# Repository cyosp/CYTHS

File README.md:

# CYTHS

A 433 MHz Temperature and Humidity Solution

This project is divided in several parts:
 * [A sensor](hardware/sensor/V2.0) which measures and sends temperature and humidity

 * [A hardware](hardware/piTransceiver/V1.0) part connected to a [Raspberry Pi](https://www.raspberrypi.org/products/) in order to:
    * Receive sensors information
    * Drive RSL switch connected to electric heaters

 * A software part hosted by the [Raspberry Pi](https://www.raspberrypi.org/products/) which:
    * Drives RSL switches

    * Stores sensors data received

    * Allow to schedule RSL switches change

    * Allow to associate and dissociate switches 

## Hardware requirement

[CYTHS](https://github.com/cyosp/CYTHS) works on [Raspberry Pi](https://www.raspberrypi.org/products/)

It has been tested on models:

 * [Pi 2 Model B](https://www.raspberrypi.org/products/raspberry-pi-2-model-b/)

   Which was used during development phase
 
 * [Pi 3 Model B](https://www.raspberrypi.org/products/raspberry-pi-3-model-b/)
 
   On this board Bluetooth has been added and connected to default UART
 
   To have it working you need:
   
   * Disable Bluetooth to restore default UART

        ```bash
        echo -e "\n# Disable Bluetooth to restore default UART\ndtoverlay=pi3-disable-bt\n" | sudo tee --append /boot/config.txt > /dev/null
        ```
   * Stop Bluetooth service

        ```bash
        sudo systemctl disable hciuart
        ```

    * Make sure you have `console=ttyAMA0` in `/boot/cmdline.txt`

   * And reboot system: `sudo reboot`

## License

**[CYTHS](https://github.com/cyosp/CYTHS)** is released under the BSD 3-Clause License.

See the bundled `LICENSE.md` for details.

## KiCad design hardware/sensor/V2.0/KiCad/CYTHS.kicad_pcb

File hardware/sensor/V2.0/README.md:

## 433 MHz Temperature and Humidity Sensor

### Printed Circuit Board (PCB)

PCB is double layers and has been:
 * Designed using: [KiCad](http://kicad-pcb.org)
 * Printed with: [OSHPARK](https://oshpark.com)

&nbsp;&nbsp;&nbsp;&nbsp;&nbsp;&nbsp;&nbsp;&nbsp;&nbsp;&nbsp;&nbsp;

### Components

| Description                     | Reference                                                                                                         | Power (V) |
|:--------------------------------|:------------------------------------------------------------------------------------------------------------------|-----------|
| Temperature and humidity sensor | [DHT22](https://www.waveshare.com/wiki/DHT22_Temperature-Humidity_Sensor)                                         | 3.3 → 6   |
| Microcontroller                 | [ATTINY85-20SU](https://www.microchip.com/en-us/product/attiny85)                                                 | 2.7 → 5.5 |
| 433 MHz transmitter             | [433 MHz transmitter](https://microcontrollerslab.com/433mhz-rf-transmitter-module-pinout-examples-applications/) | 3.3 → 12  |
| 3x 1.5V AAA batteries           | [Camelion batteries](http://camelionbatteries.com/primary/plus.html)                                              | 1.5       |

#### ATtiny85 pin mapping

```
PB5 -| °   |- VCC
PB3 -|     |- PB2
PB4 -|     |- PB1
GND -|     |- PB0
```

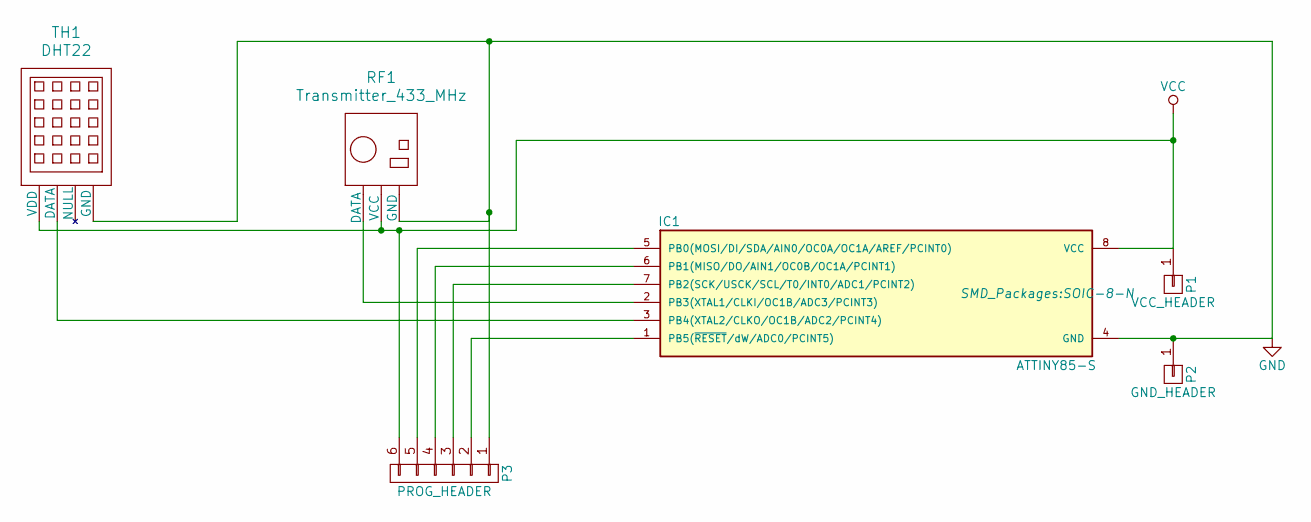
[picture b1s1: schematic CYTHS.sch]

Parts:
IC1: ATTINY85-S; SOIC-8-N
P1: VCC_HEADER; Pin_Header_Straight_1x01
P2: GND_HEADER; Pin_Header_Straight_1x01
P3: PROG_HEADER; Pin_Header_Angled_1x06
RF1: Transmitter_433_MHz; RF_Transmitter_433_MHz
TH1: DHT22; DHT22_Temperature_Humidity

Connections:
GND: IC1.4 (GND), P2.1, P3.1, RF1.3 (GND), TH1.4 (GND)
unnamed: IC1.1 (PB5(~RESET~/dW/ADC0/PCINT5)), P3.2
unnamed: IC1.2 (PB3(XTAL1/CLKI/OC1B/ADC3/PCINT3)), RF1.1 (DATA)
unnamed: IC1.3 (PB4(XTAL2/CLKO/OC1B/ADC2/PCINT4)), TH1.2 (DATA)
unnamed: IC1.5 (PB0(MOSI/DI/SDA/AIN0/OC0A/OC1A/AREF/PCI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), P3.5
unnamed: IC1.6 (PB1(MISO/DO/AIN1/OC0B/OC1A/PCINT1)), P3.4
unnamed: IC1.7 (PB2(SCK/USCK/SCL/T0/INT0/ADC1/PCINT2)), P3.3
VCC: IC1.8 (VCC), P1.1, P3.6, RF1.2 (VCC), TH1.1 (VDD)

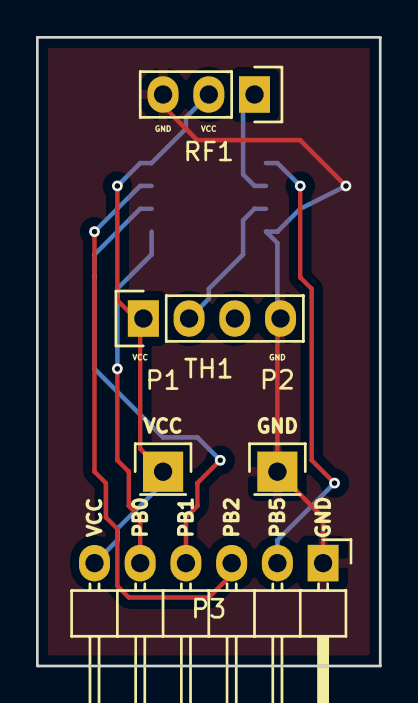
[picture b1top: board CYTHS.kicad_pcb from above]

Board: 2 copper layers, 19.0 x 34.9 mm, 6 parts (1 on the bottom side), 8 nets.

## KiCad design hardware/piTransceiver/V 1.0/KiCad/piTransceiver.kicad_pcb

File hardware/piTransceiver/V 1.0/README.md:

## piTransceiver

[Raspberry Pi](https://www.raspberrypi.org/products/) extension board to receive and transmit to 433MHz.

#### PCB

piTransceiver is composed of a double layer PCB:

&nbsp;&nbsp;&nbsp;&nbsp;&nbsp;&nbsp;&nbsp;&nbsp;&nbsp;&nbsp;&nbsp;

### Components

Components used are:

| Component | Reference                            |
|:----------|:-------------------------------------|
| R1        | 2.2 KΩ 5%                            |
| R2        | 27 Ω 5%                              |
| LED       | Yellow LED                           |
| IC1       | ATtiny85-20PU                        |
| RF1       | 433 MHz transmitter + spring antenna |
| RF2       | 433 MHz receiver + spring antenna    |

#### Configuration

These steps will configure Arduino software in order to use the microcontroller running at 16 Mhz:
 * File -> Preferences
  * In *Additional Boards Manager URLs:*
  * Enter *https://raw.githubusercontent.com/damellis/attiny/ide-1.6.x-boards-manager/package_damellis_attiny_index.json*
  * And *OK* button
 * Tools -> Board-> Boards Manager...
    * Search in the list and select: **attiny** by **David A. Mellis**
    * Click *Install*
    * And *Close* button
 * Tools -> Board-> ATtiny25/45/85
 * Tools -> Processor-> ATtiny85
 * Tools -> Clock-> Internal 16 MHz
 * Tools -> Programmer-> USBtinyISP

Then it's necessary to burn fuses of the microcontroller to set this configuration.
Steps are:
 * Plug a microcontroller on the [Tiny AVR Programmer](https://www.sparkfun.com/products/11801)
 * Plug the [Tiny AVR Programmer](https://www.sparkfun.com/products/11801) to the computer
 * Tools -> Burn Bootloader

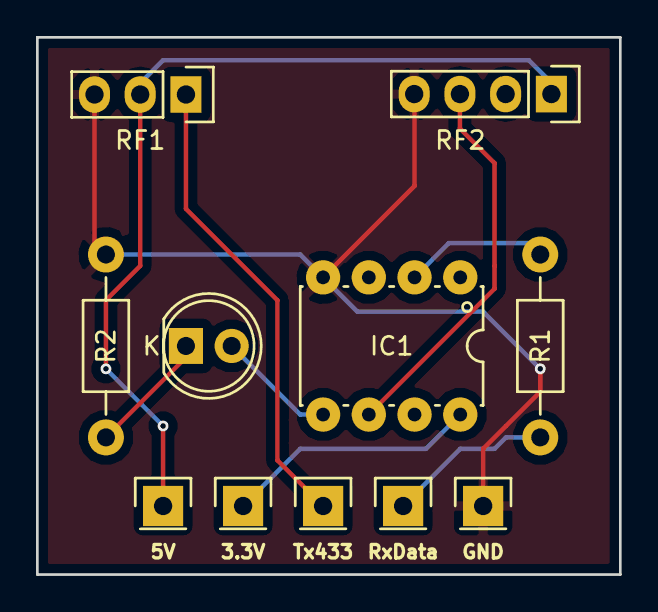
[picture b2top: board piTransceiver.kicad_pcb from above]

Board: 2 copper layers, 32.4 x 29.8 mm, 5 parts (0 on the bottom side), 4 nets.

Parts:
IC1: ATTINY85-S; PDIP-8
R1, R2: Resistor_Horizontal_RM10mm
RF1: RF_Transmitter_433_MHz
RF2: RF_Receiver_433_MHz

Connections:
+5V: RF1.2, RF2.1
GND: IC1.4, R2.1, RF1.3, RF2.4
unnamed: IC1.2, R1.1
unnamed: IC1.6, RF2.3

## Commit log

2016-03-16 Update README file
2016-03-17 Improve project description
2016-03-26 Improve README file
2016-04-05 Add components used and code details
2016-04-06 Add microcontroller source code
2016-04-07 Add PCB source code
2016-04-14 Improve battery life
2016-04-18 Add Arduino microcontroller configuration
2016-04-25 Add PCB image
2016-05-22 Improve sensor id random generation
2016-06-17 Transmission period is now set to 5 minutes
2016-07-03 Repository aim is expanded
2016-07-03 Reorganize sensor code
2016-07-06 Add cyths-receiver and its makefile
2016-07-07 Add software JSON configuration file
2016-07-07 Add a first web server part
2016-07-07 Update creation dates
2016-07-07 Manage web folder via makefile
2016-07-07 Add cyths-receiver as a service
2016-07-08 Add http://localhost/cyths/sensors
2016-07-08 Manage 'id' parameter for http://localhost/cyths/sensors
2016-07-10 Add a graphic link to each sensor
2016-07-12 Update README thus sensor data format
2016-07-12 Improve README display
2016-07-13 Reflect new sensor data format
2016-07-16 Improve Arduino configuration details
2016-07-21 Switch receiver serial port and add log rotation
2016-08-01 Prepare new sensor hardware
2016-08-28 Add CYTHS 2.0 PCB images
2016-08-29 Add KiCad files for CYTHS 2.0 sensor
2016-08-30 Add CYTHS V 2.0 Arduino firmware
2016-09-04 Add piTransceiver hardware
2016-09-07 Add piTransceiver V 1.0 Arduino firmware
2016-09-09 Add hyperlinks to CYTHS sensor and piTransceiver
2016-09-09 Add piTransceiver README file
2016-09-10 Remove README.md of hyperlinks
2016-09-10 Update README.md files
2016-09-18 Display sensor V 2.0
2016-09-18 Reduce image weight
2016-09-18 Update images layout
2016-09-25 Add batteries lifetime details
2016-09-25 Add piTransceiver photos
2016-09-25 Add piTransceiver components list
2016-09-26 Add piTransceiver microcontroller configuration
2016-09-28 Switch can now be disabled
2016-09-29 Manage cURL return code
2016-09-30 Create dedicated info API
2016-10-01 Add spring antenna
2016-10-02 Fix: call to "switch" URL API
2016-10-03 Add cyths-transmitter
2016-10-04 Update default page "title"
2016-10-04 Restore creation date
2016-10-05 Add sample of crontab configuration
2016-10-05 Update page title configuration value
2016-10-06 Add crontab display page
2016-10-07 Sensor graph takes now all page width
2016-10-08 Add cron-expression PHP library
2016-10-08 Update crontab configuration format
2016-10-09 Add crontab service
2016-10-10 Add cronwtf JavaScript library
2016-10-10 Use cronwtf library
2016-10-16 Add bootstrap navbar
2016-10-17 Add dygraphs JavaScript library
2016-10-19 Add i18next JavaScript library
2016-10-20 Add Font-Awesome library
2016-10-21 Use internationalization and Font-Awesome
2016-10-21 Create data folder is no more necessary
2016-10-22 Call cythsInit function after internationalization
2016-10-22 Update sensors web page
2016-10-23 Remove useless h1 tag
2016-10-23 Reorganize code: add addSwitch function
2016-10-24 UI is now refreshed when page has focus
2016-10-25 Fix: Refresh UI on mobile browser
2016-10-25 Add an automatic refresh each 5 seconds
2016-10-26 Add version in navigation bar
2016-10-26 Add jqCron JavaScript library
2016-10-26 Use jqCron library instead of cronwtf
2016-10-26 Improve usage of page width
2016-10-27 Call cythsBeforeLocalize function before internationalization
2016-10-27 Localize "on" and "off" crontab states
2016-10-28 Crontab are padded with zero
2016-10-28 Add crontab translation
2016-10-28 Optimize code
2016-10-28 Display loading icon in waiting page is loaded
2016-10-29 Add jqCron default translations
2016-10-29 States are displayed as jqCron
2016-10-29 Use now one line per crontab
2016-10-30 Enable crontab to be modified without saving modification
2016-10-31 Detect crontab user change
2016-11-01 User can now update a crontab configuration
2016-11-01 pageTitle property is no more used
2016-11-02 Add sensors entry in navigation bar
2016-11-03 Remove cronwtf library
2016-11-04 Manage language more than 2 characters
2016-11-05 Update main web page
2016-11-06 Add scheduler page screenshot
2016-11-12 Add missing 0 for: -.9 <= TEMPERATURE <= .9
2016-11-17 Errors are now logged in footer
2016-12-27 It's now possible to disable a crontab entry
2016-12-27 Disabled state is now shown during loading phase
2017-01-30 Manage switch with only a sensor attached
2017-03-22 Update configuration file structure
2017-03-22 Update following new configuration file structure
2017-03-24 Allow to store sensor data
2017-03-24 Fix: JavaScript error: switchConfigured.sensor is undefined
2017-03-27 Update time format
2017-03-27 Allow to configure sensor info displayed
2017-03-27 Humidity is an integer
2017-03-27 Use new API: /API/set/sensor/data/
2017-03-28 Add crontab condition
2017-03-28 Add sample crontab condition
2017-03-28 Manage crontab condition
2017-03-28 Add README : CYTHS - Software solution
2017-03-30 Switch nodejs binary name from node to nodejs
2017-03-30 Add nodejs crontab-condition script
2017-03-30 Use NODE_PATH variable to know where are stored modules
2017-03-30 Fix: Check sensor existence before to check sensor.id
2017-03-30 Update cyths.js version
2017-03-31 Add return code description
2017-03-31 Fix: PHP parse error
2017-03-31 Index is now starting 0 instead of 1
2017-04-04 Manage empty switch info field
2017-04-04 Remove unnecessary test
2017-04-05 Display crontab condition
2017-04-12 Disable crontab condition if needed
2017-07-03 Improve error messages
2017-07-06 Add unauthorized error message
2017-07-13 Remove space in directory names
2017-08-22 Add admin page
2017-08-23 Add optional repeat argument
2017-08-23 Add pairing display in admin page
2017-08-24 Add pairing interactive part
2017-08-25 Check emitterWiringPiNumber and repeat received values
2017-08-26 Introduce desapairing feature
2017-08-27 Major version with association and dissociation features
2017-08-28 Update home page screenshot
2017-08-29 Clean home page screenshot
2017-08-30 Update scheduler screenshot and add admin page screenshot
2018-09-13 Add hardware requirement
2018-09-15 Fix: display switches in loading page instead of the first data refresh
2019-01-19 Log battery percentage value
2019-01-20 Set battery percentage in sensor data
2019-01-20 Battery percentage and indicator can be displayed in sensor info zone
2019-01-21 Fix: Minimum and maximum battery level was inverted
2019-01-22 Store battery percentage inside Round Robin Database
2019-01-23 Add battery percentage to graphics
2019-01-30 Provide a demo web server
2019-02-02 Add sensors data to complete demo
2019-02-03 Add demo usage note
2021-02-13 Remove useless spaces
2021-02-14 Fix: No default switch info label translated when there is no sensor
2021-02-14 Improve switch info default label translation mechanism
2021-02-18 Add iOS native application behavior on home screen
2021-11-28 Use rc-rsl without sudo
2022-08-08 Add dependency libraries installation for sensor V2.0
2022-08-08 Update Arduino configuration + add details on programmer setup and code upload
2022-08-09 Update component links and add power voltage
2022-08-09 Update microcontroller frequency
2022-08-09 Add warning on programmer linked to sensor board
2022-08-09 Add burn bootloader output example
2022-08-10 Sensor id can be chosen using a static variable
2022-08-11 Battery level is updated only each 6 hours instead of each measure
2022-08-12 README restricted to only hardware parts
2022-08-12 Use an unique place for microcontroller firmware source code
2022-08-12 Add README to sensor
2022-08-13 Improve battery voltage mapping and fact it can only down
2022-08-14 Fix: Code not working for sensor V1.0
2022-08-15 Update code re-upload section
2022-08-16 Use NaN as value for CSV lines where no data has been received
2022-08-17 Display sensors raw data instead of smoothed ones
2022-08-18 Add ATtiny85 pin mapping
2022-08-20 Improve navigation bar
2022-08-21 Add favicon and remove CYTHS in page titles
2022-08-22 Improve page view and vertical scroll on phone screens
2022-08-23 Update how version is displayed and remove useless hyperlink
2022-10-03 View can be split via configuration `$.view.splitMode=true`
2022-10-03 Hide switch with no sensor from sensor view in split mode
2022-10-06 Fix: Switch not displayed on page load
2022-10-11 Update switch info color following outdated sensor data
2022-10-15 Sensor temperature and/or humidity trend can be displayed in info section
2022-12-19 Fix: Incorrect temperature trend with negative values
2023-07-12 Log received code as decimal value
2023-07-15 Add JSONPath library
2023-07-15 Move crontab condition from NodeJS/json-query to PHP/JSONPath
2023-07-16 Add missing properties
2023-07-17 Remove individual release files
2023-07-17 Fix: Incorrect require path for JSONPath library
2023-07-20 Move to container packaging
2023-07-22 Add endpoint to update CYTHS value
2023-07-22 Fix: Display all sensors graph instead of the asked one
2023-07-31 [cyths-receiver] Check ttyS1 availability if ttyAMA0 doesn't exist
2023-07-31 Automate container image generation
2023-07-31 Add arm64v8 container image generation
2023-08-01 cyths-update: Avoid Bash error if sensor value received is not registered
2023-08-03 Build container image with empty cyths-update log file
2023-08-03 Update to work behind a reverse proxy
2023-08-07 Build container image with rc-rsl 2.1.0
2023-08-07 Expose csv and rrd directories as container image volumes
2023-08-25 Set local time and time zone according to TZ variable
2023-09-28 Update endpoint can take several values
2023-10-22 Fix: Temperature matching with value sent
2023-10-23 Add flood sensor capability to V2 sensor
2023-10-24 Add first flood sensor extension description
2023-12-24 Add switch separator and switch with sensor in splited view
2024-03-17 Add optional step up module
2024-08-09 cyths-update: Move updated date to sensor decoded info in a new log format
